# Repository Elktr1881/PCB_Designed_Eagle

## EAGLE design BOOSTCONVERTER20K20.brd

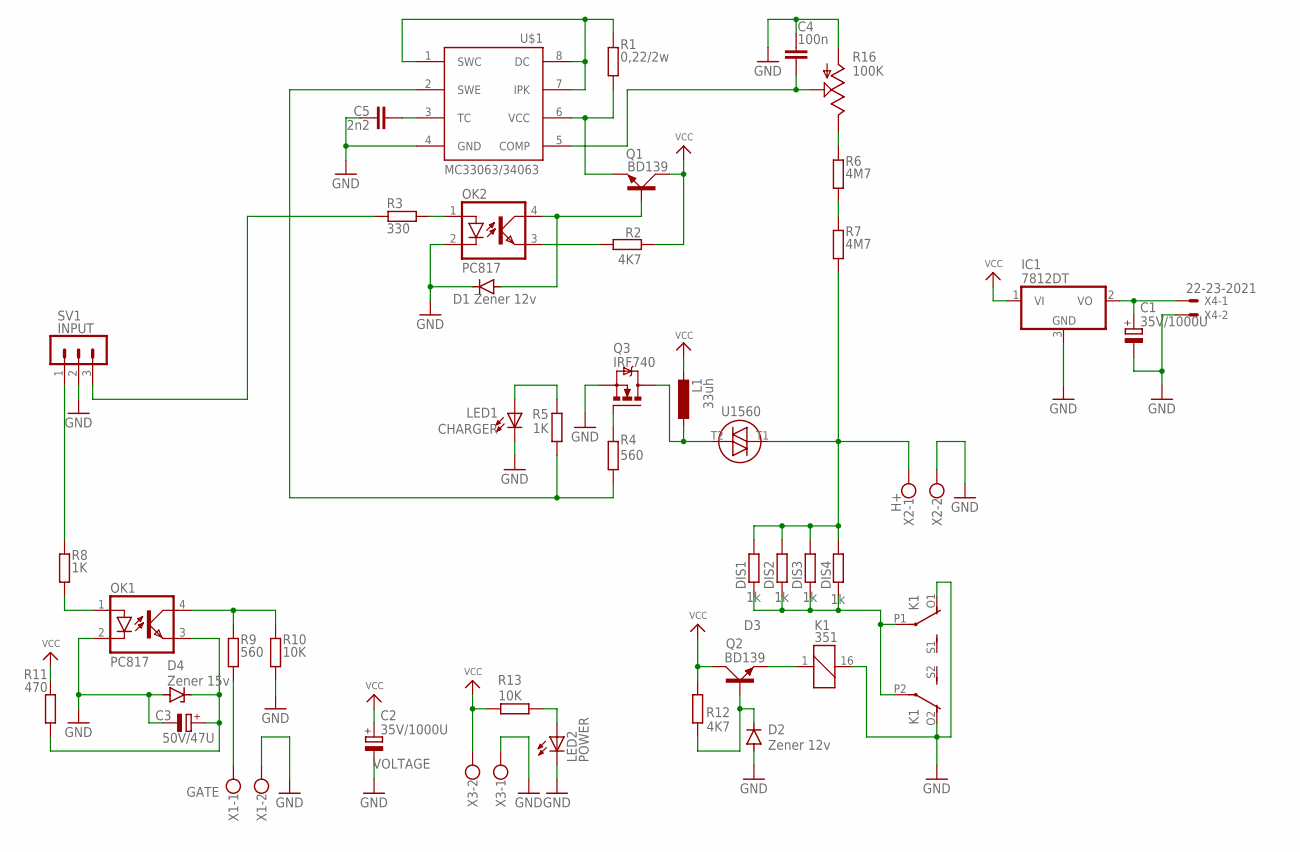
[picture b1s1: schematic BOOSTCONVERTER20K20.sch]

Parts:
C1, C2: 35V/1000U; E2,5-7
C3: 50V/47U; 153CLV-0810
C4: 100n; C0805K
C5: 2n2; C0805K
D1, D2: Zener 12v; DO35-7
D3: U1560; BR210S
D4: Zener 15v; DO35Z10
DIS1, DIS2, DIS3, DIS4: 1k; VTA53
IC1: 7812DT; TO252
K1: 351
L1: 33uh; TJ3-U2
LED1: CHARGER; LED_1206
LED2: POWER; LED_1206
OK1, OK2: PC817; DIL04
Q1, Q2: BD139; TO126AV
Q3: IRF740; TO220BV
R1: 0,22/2w; M1206
R2, R12: 4K7; M1206
R3: 330; M1206
R4, R9: 560; M1206
R5, R8: 1K; M1206
R6, R7: 4M7; 0309/10
R10, R13: 10K; M1206
R11: 470; M1206
R16: 100K; CA6V
SV1: INPUT; MA03-1
U$1: MC33063/MC34063D; SO08
X1: GATE; W237-102
X2: H+; W237-102
X3: VOLTAGE; W237-102
X4: 22-23-2021

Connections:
GND: C1.-, C2.-, C3.-, C4.1, C5.1, D1.C, D2.A, D4.A, IC1.3 (GND), K1.16 (2), K1.O1 (O), K1.O2 (O), LED1.C, LED2.C, OK1.2 (C), OK2.2 (C), Q3.S, R10.1, R16.A, SV1.2, U$1.4 (GND), X1.2, X2.2, X3.1, X4.2
unnamed: R1.2, U$1.1 (SWC), U$1.7 (IPK), U$1.8 (DC)
unnamed: Q1.E, R1.1, U$1.6 (VCC)
unnamed: D1.A, OK2.4 (COL), Q1.B
unnamed: OK2.3 (EMIT), R2.2
unnamed: R8.1, SV1.1
unnamed: OK2.1 (A), R3.2
unnamed: D3.T2, L1.1, Q3.D
unnamed: C4.2, R16.S, U$1.5 (COMP)
unnamed: K1.1, Q2.E
unnamed: C5.2, U$1.3 (TC)
unnamed: LED1.A, R5.2
unnamed: R6.1, R7.2
unnamed: Q3.G, R4.1
unnamed: R3.1, SV1.3
unnamed: R6.2, R16.E
unnamed: DIS1.1, DIS2.1, DIS3.1, DIS4.1, K1.P1, K1.P2
unnamed: OK1.1 (A), R8.2
unnamed: OK1.4 (COL), R9.2, R10.2
unnamed: C3.+, D4.C, OK1.3 (EMIT), R11.1
unnamed: D2.C, Q2.B, R12.1
unnamed: R9.1, X1.1
unnamed: LED2.A, R13.1
unnamed: R4.2, R5.1, U$1.2 (SWE)
unnamed: D3.T1, DIS1.2, DIS2.2, DIS3.2, DIS4.2, R7.1, X2.1
unnamed: C1.+, IC1.2 (VO), X4.1
VCC: C2.+, IC1.1 (VI), L1.2, Q1.C, Q2.C, R2.1, R11.2, R12.2, R13.2, X3.2

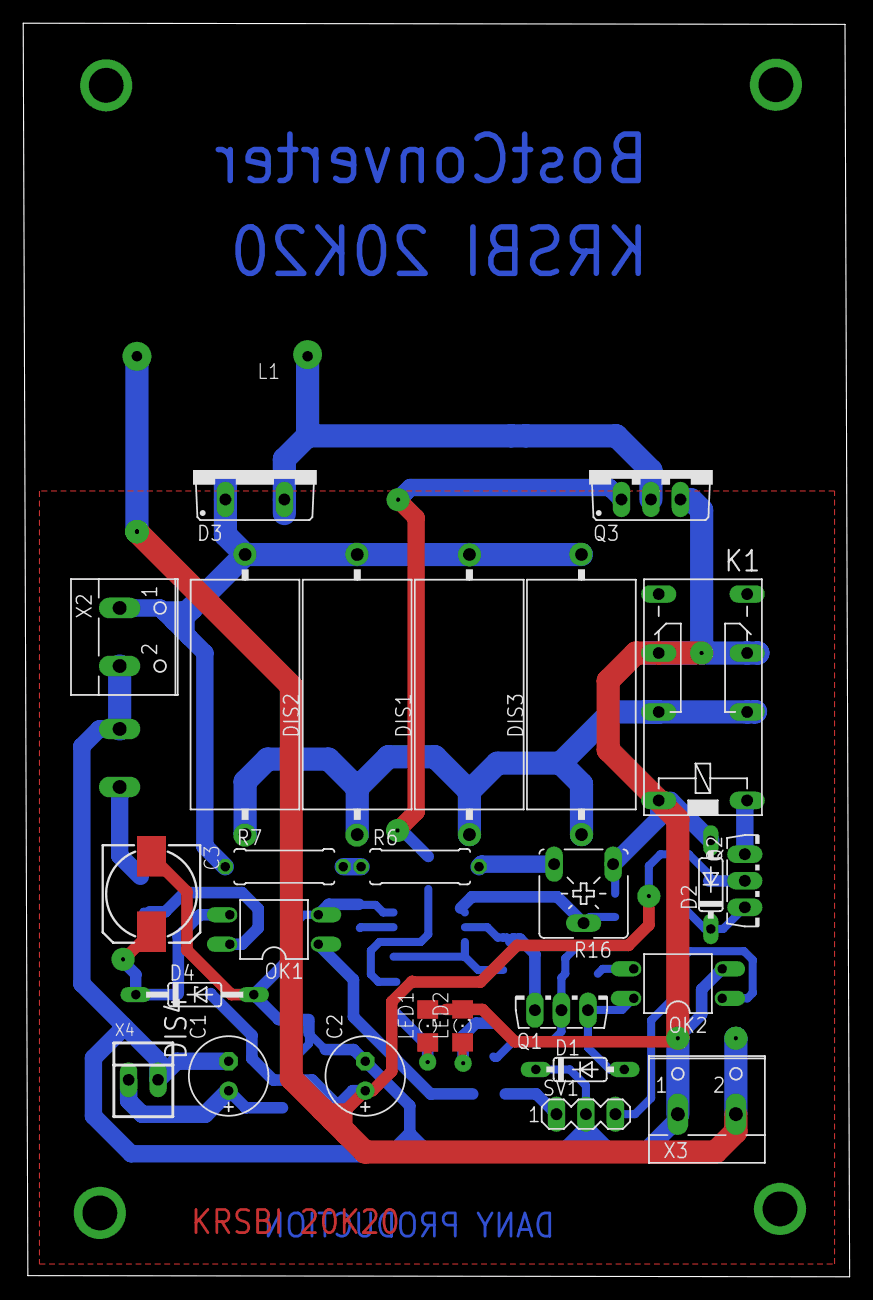
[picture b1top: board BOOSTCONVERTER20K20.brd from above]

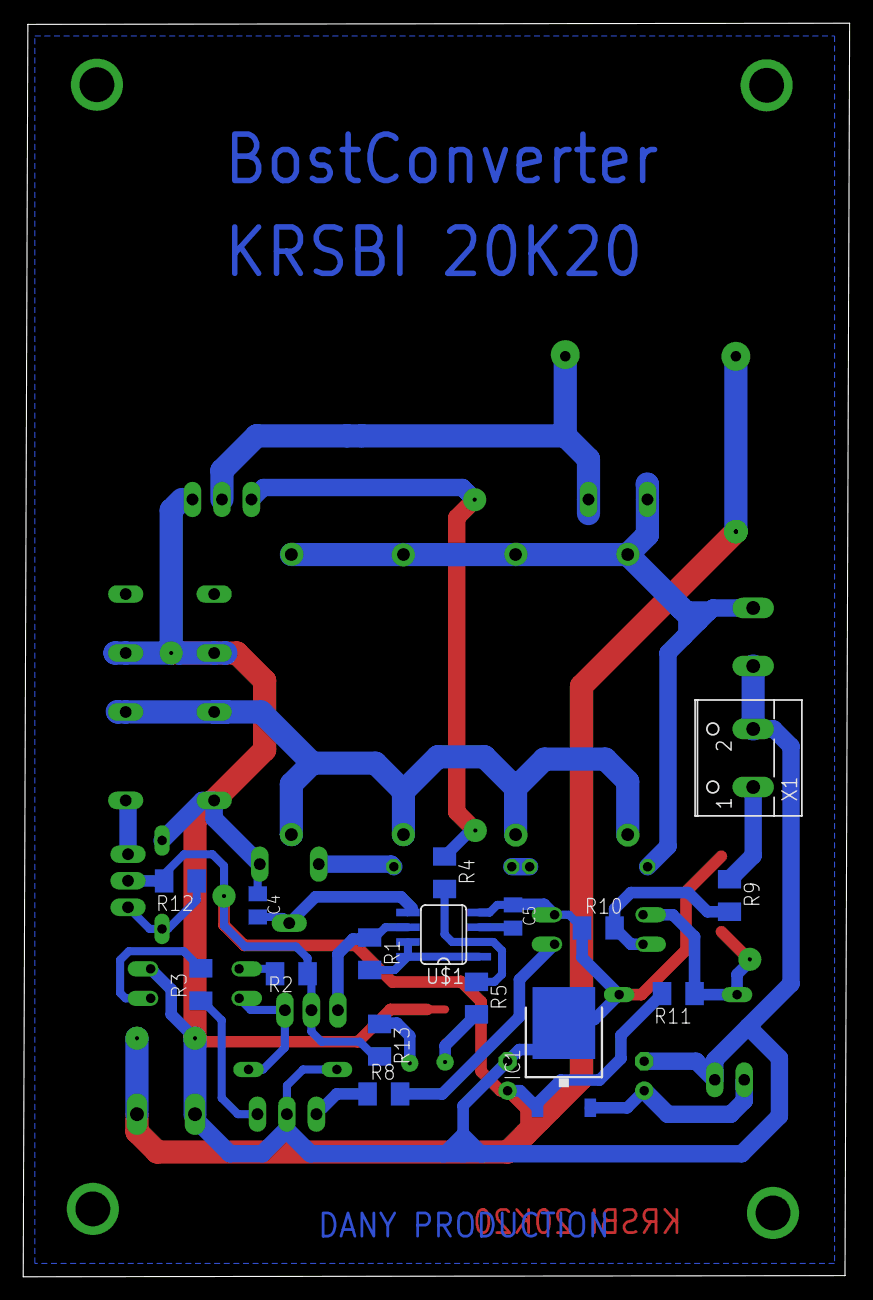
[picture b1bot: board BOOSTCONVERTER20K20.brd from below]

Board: 2 copper layers, 71.2 x 108.0 mm, 43 parts (16 on the bottom side), 27 nets.

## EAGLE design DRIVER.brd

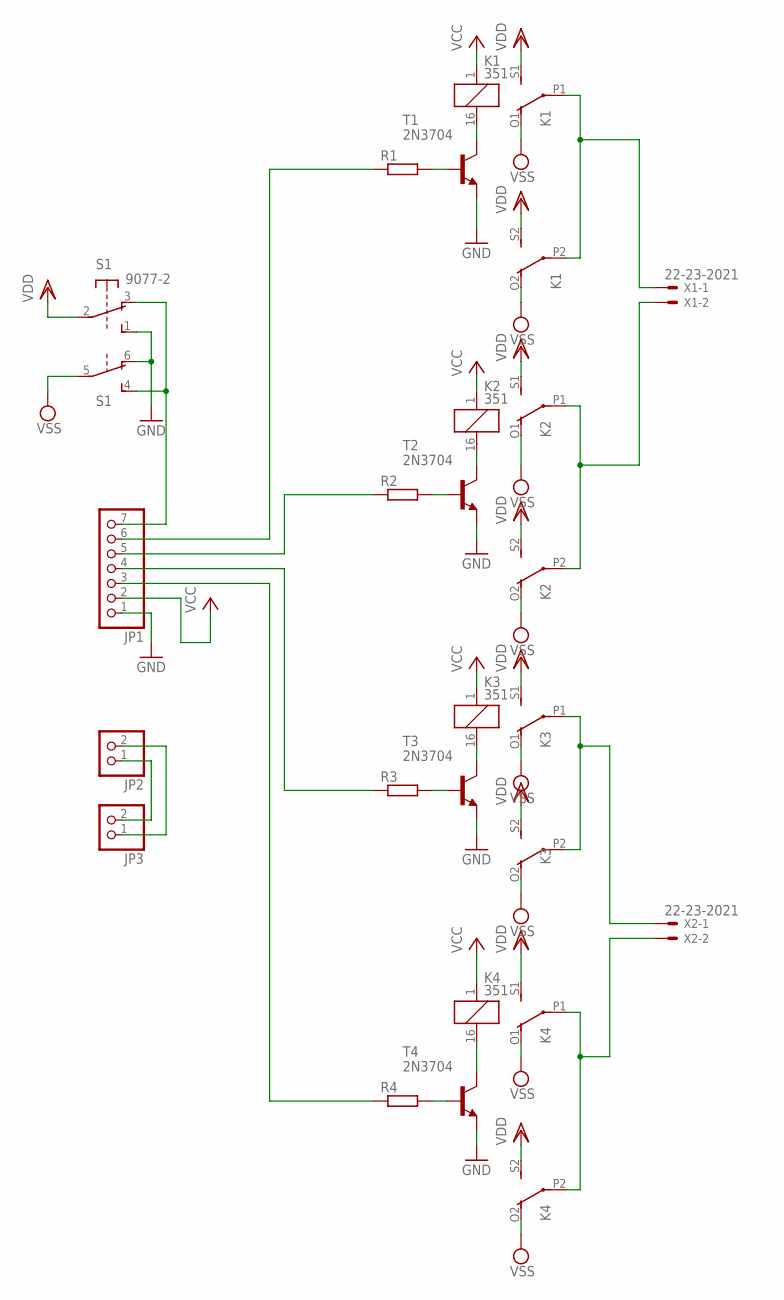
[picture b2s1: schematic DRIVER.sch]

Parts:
JP1: PINHD-1X7; 1X07
JP2, JP3: PINHD-1X2; 1X02
K1, K2, K3, K4: 351
R1, R2, R3, R4: R-EU_0207/7; 0207/7
S1: 9077-2
T1, T2, T3, T4: 2N3704; TO92
X1, X2: 22-23-2021

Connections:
GND: JP1.1, S1.1 (S), S1.6 (O), T1.3 (E), T2.3 (E), T3.3 (E), T4.3 (E)
unnamed: K1.16 (2), T1.2 (C)
unnamed: K2.16 (2), T2.2 (C)
unnamed: K4.16 (2), T4.2 (C)
unnamed: K3.P1, K3.P2, X2.1
unnamed: K4.P1, K4.P2, X2.2
unnamed: K1.P1, K1.P2, X1.1
unnamed: K2.P1, K2.P2, X1.2
unnamed: JP1.5, R2.1
unnamed: JP1.4, R3.1
unnamed: JP1.3, R4.1
unnamed: K3.16 (2), T3.2 (C)
unnamed: R4.2, T4.1 (B)
unnamed: R3.2, T3.1 (B)
unnamed: R2.2, T2.1 (B)
unnamed: R1.2, T1.1 (B)
unnamed: JP1.6, R1.1
unnamed: JP2.2, JP3.1
unnamed: JP1.7, S1.3 (O), S1.4 (S)
unnamed: JP2.1, JP3.2
VCC: JP1.2, K1.1, K2.1, K3.1, K4.1
VDD: K1.S1 (S), K1.S2 (S), K2.S1 (S), K2.S2 (S), K3.S1 (S), K3.S2 (S), K4.S1 (S), K4.S2 (S), S1.2
VSS: K1.O1 (O), K1.O2 (O), K2.O1 (O), K2.O2 (O), K3.O1 (O), K3.O2 (O), K4.O1 (O), K4.O2 (O), S1.5

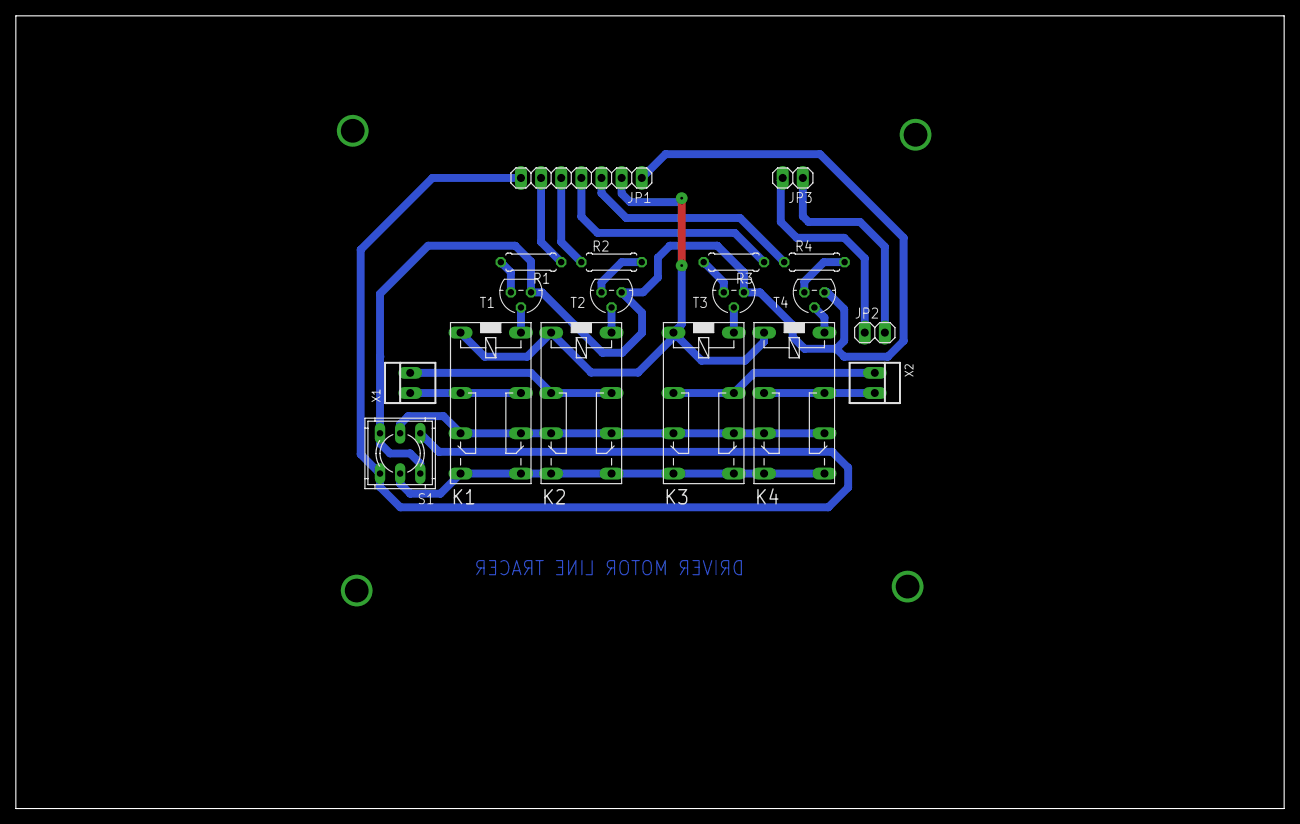
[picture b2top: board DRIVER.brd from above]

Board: 2 copper layers, 160.0 x 100.0 mm, 18 parts (0 on the bottom side), 23 nets.
